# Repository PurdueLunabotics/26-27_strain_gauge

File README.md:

# Strain gauge amplifier

A strain gauge amplifer, designed to get useful readings out of a strain gauge sensor.
Specific sensor still TBD

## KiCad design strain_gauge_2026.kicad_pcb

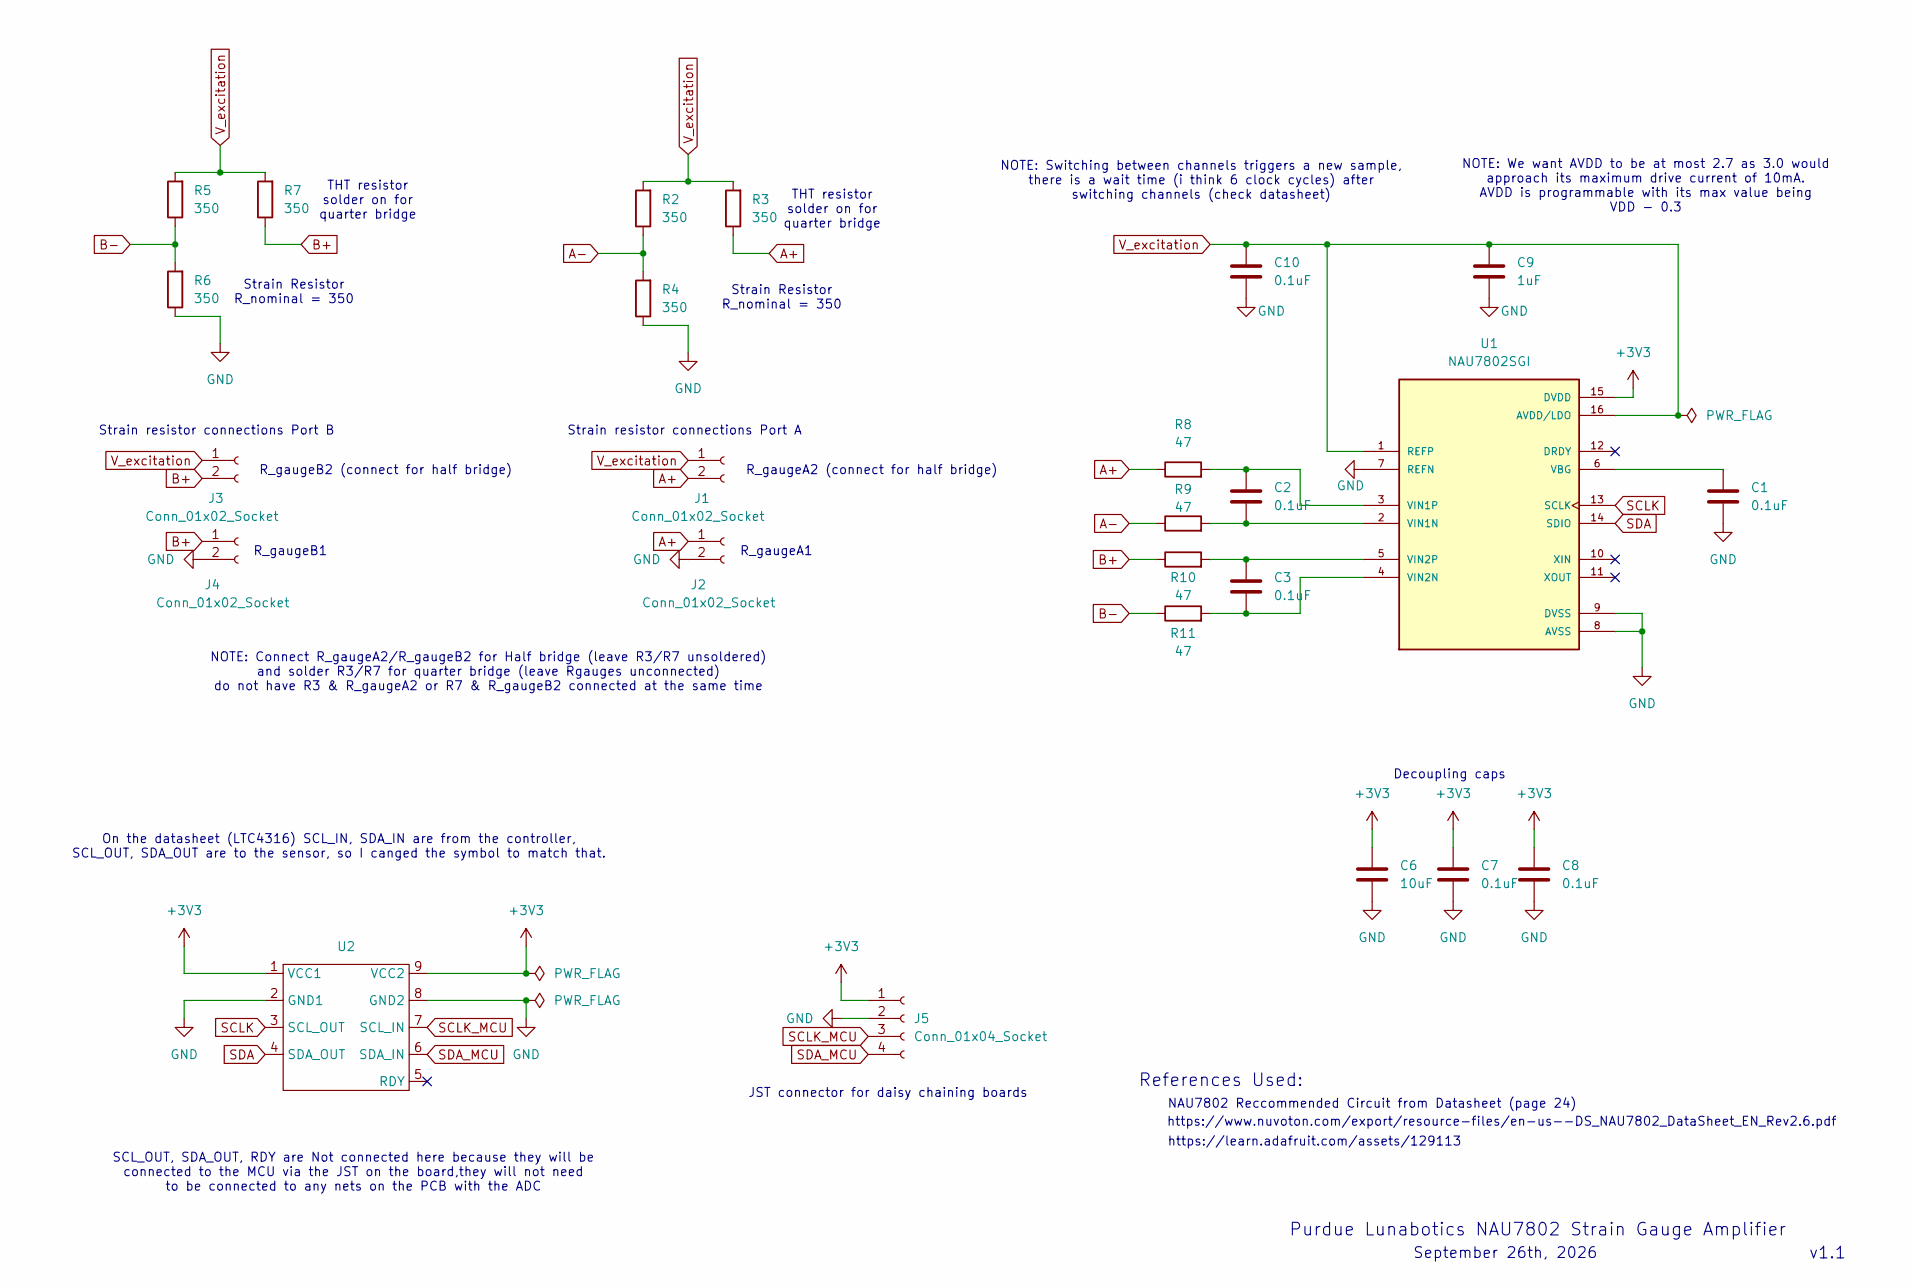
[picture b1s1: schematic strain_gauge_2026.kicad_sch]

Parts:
C1, C2, C3, C7, C8, C10: 0.1uF; C_0805_2012Metric_Pad1.18x1.45mm_HandSolder
C6: 10uF; C_0805_2012Metric_Pad1.18x1.45mm_HandSolder
C9: 1uF; C_0805_2012Metric_Pad1.18x1.45mm_HandSolder
J1, J2, J3, J4: Conn_01x02_Socket; PinHeader_1x02_P2.54mm_Vertical
J5: Conn_01x04_Socket; PinHeader_1x04_P2.54mm_Vertical
R2, R3, R4, R5, R6, R7: 350; R_Axial_DIN0207_L6.3mm_D2.5mm_P10.16mm_Horizontal
R8, R9, R10, R11: 47; R_Axial_DIN0207_L6.3mm_D2.5mm_P10.16mm_Horizontal
U1: NAU7802SGI; DIP-16_W7.62mm; PARTREV 2.6
U2: DFR1193

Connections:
+3V3: C6.1, C7.1, C8.1, J5.1, U1.15 (DVDD), U2.1 (VCC1), U2.9 (VCC2); also elsewhere on the board
A+: J1.2, J2.1, R3.1, R8.1
A-: R2.1, R4.2, R9.1
B+: J3.2, J4.1, R7.1, R10.1
B-: R5.1, R6.2, R11.1
GND: C1.2, C6.2, C7.2, C8.2, C9.2, C10.2, J2.2, J4.2, J5.2, R4.1, R6.1, U1.7 (REFN), U1.8 (AVSS), U1.9 (DVSS), U2.2 (GND1), U2.8 (GND2); also elsewhere on the board
unnamed: C1.1, U1.6 (VBG)
unnamed: C2.2, R9.2, U1.2 (VIN1N)
unnamed: C2.1, R8.2, U1.3 (VIN1P)
unnamed: C3.2, R11.2, U1.4 (VIN2N)
unnamed: C3.1, R10.2, U1.5 (VIN2P)
SCLK: U1.13 (SCLK), U2.3 (SCL_OUT); also elsewhere on the board
SCLK_MCU: J5.3, U2.7 (SCL_IN); also elsewhere on the board
SDA: U1.14 (SDIO), U2.4 (SDA_OUT); also elsewhere on the board
SDA_MCU: J5.4, U2.6 (SDA_IN); also elsewhere on the board
V_excitation: C9.1, C10.1, J1.1, J3.1, R2.2, R3.2, R5.2, R7.2, U1.1 (REFP), U1.16 (AVDD/LDO)

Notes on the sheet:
R_gaugeA1
Strain resistor connections Port A
Strain Resistor R_nominal = 350
R_gaugeB1
Decoupling caps
R_gaugeB2 (connect for half bridge)
R_gaugeA2 (connect for half bridge)
NAU7802 Reccommended Circuit from Datasheet (page 24)
v1.1
JST connector for daisy chaining boards
NOTE: Connect R_gaugeA2/R_gaugeB2 for Half bridge (leave R3/R7 unsoldered) and solder R3/R7 for quarter bridge (leave Rgauges unconnected) do not have R3 & R_gaugeA2 or R7 & R_gaugeB2 connected at the same time
Purdue Lunabotics NAU7802 Strain Gauge Amplifier
https://www.nuvoton.com/export/resource-files/en-us--DS_NAU7802_DataSheet_EN_Rev2.6.pdf
NOTE: We want AVDD to be at most 2.7 as 3.0 would approach its maximum drive current of 10mA. AVDD is programmable with its max value being VDD - 0.3
SCL_OUT, SDA_OUT, RDY are Not connected here because they will be connected to the MCU via the JST on the board,they will not need to be connected to any nets on the PCB with the ADC
September 26th, 2026
THT resistor solder on for quarter bridge
https://learn.adafruit.com/assets/129113
NOTE: Switching between channels triggers a new sample, there is a wait time (i think 6 clock cycles) after switching channels (check datasheet)
On the datasheet (LTC4316) SCL_IN, SDA_IN are from the controller, SCL_OUT, SDA_OUT are to the sensor, so I canged the symbol to match that.
References Used:
Strain resistor connections Port B

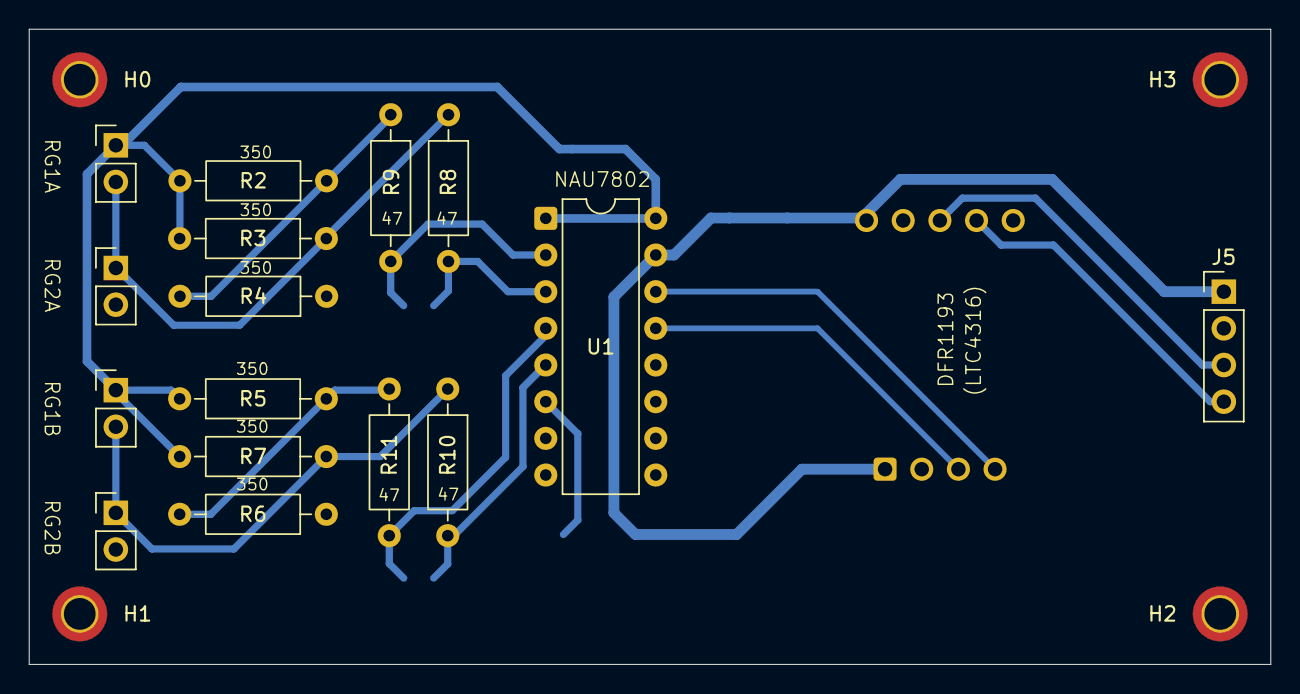
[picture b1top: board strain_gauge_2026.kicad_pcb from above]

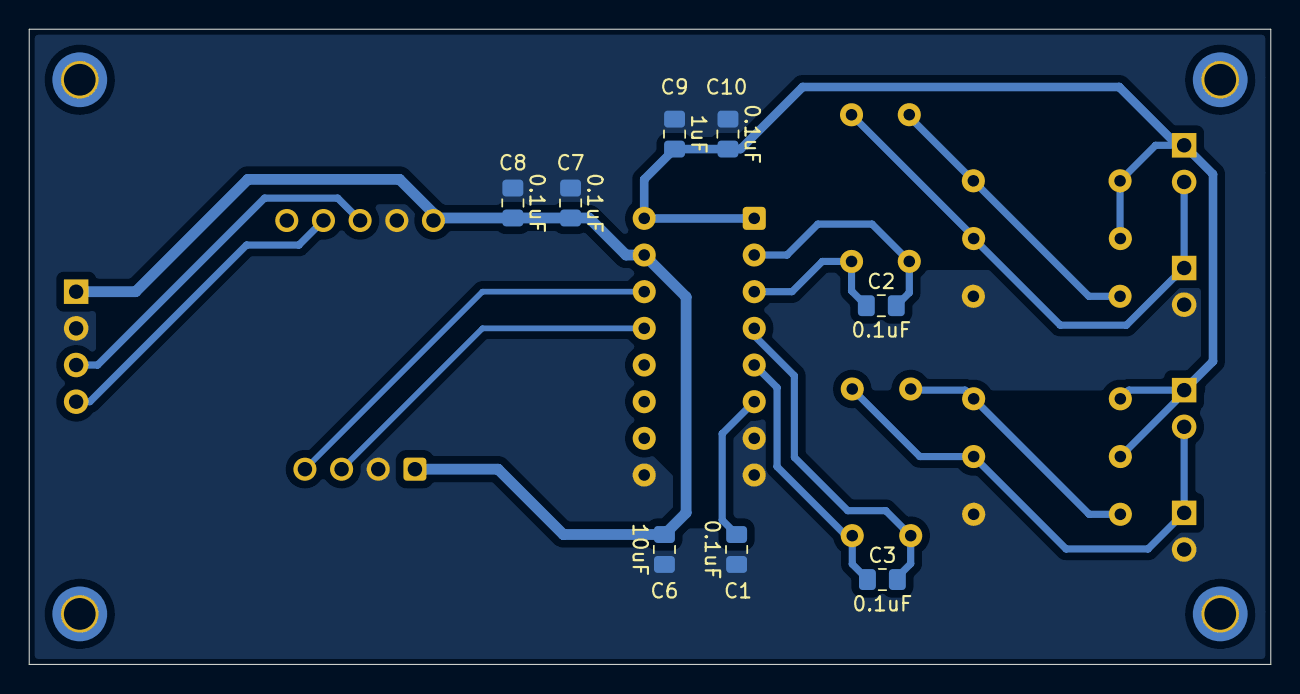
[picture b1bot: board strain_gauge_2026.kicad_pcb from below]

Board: 2 copper layers, 86.0 x 44.0 mm, 29 parts (8 on the bottom side), 16 nets.

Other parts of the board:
DFR1193: DFR1193
H0, H1, H2, H3: MountingHole_2.2mm_M2_DIN965_Pad_TopBottom

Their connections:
+3V3: DFR1193.1 (VCC1), DFR1193.9 (VCC2); also elsewhere on the board
GND: DFR1193.2 (GND1), DFR1193.8 (GND2); also elsewhere on the board
SCLK: DFR1193.3 (SCL_OUT); also elsewhere on the board
SCLK_MCU: DFR1193.7 (SCL_IN); also elsewhere on the board
SDA: DFR1193.4 (SDA_OUT); also elsewhere on the board
SDA_MCU: DFR1193.6 (SDA_IN); also elsewhere on the board
